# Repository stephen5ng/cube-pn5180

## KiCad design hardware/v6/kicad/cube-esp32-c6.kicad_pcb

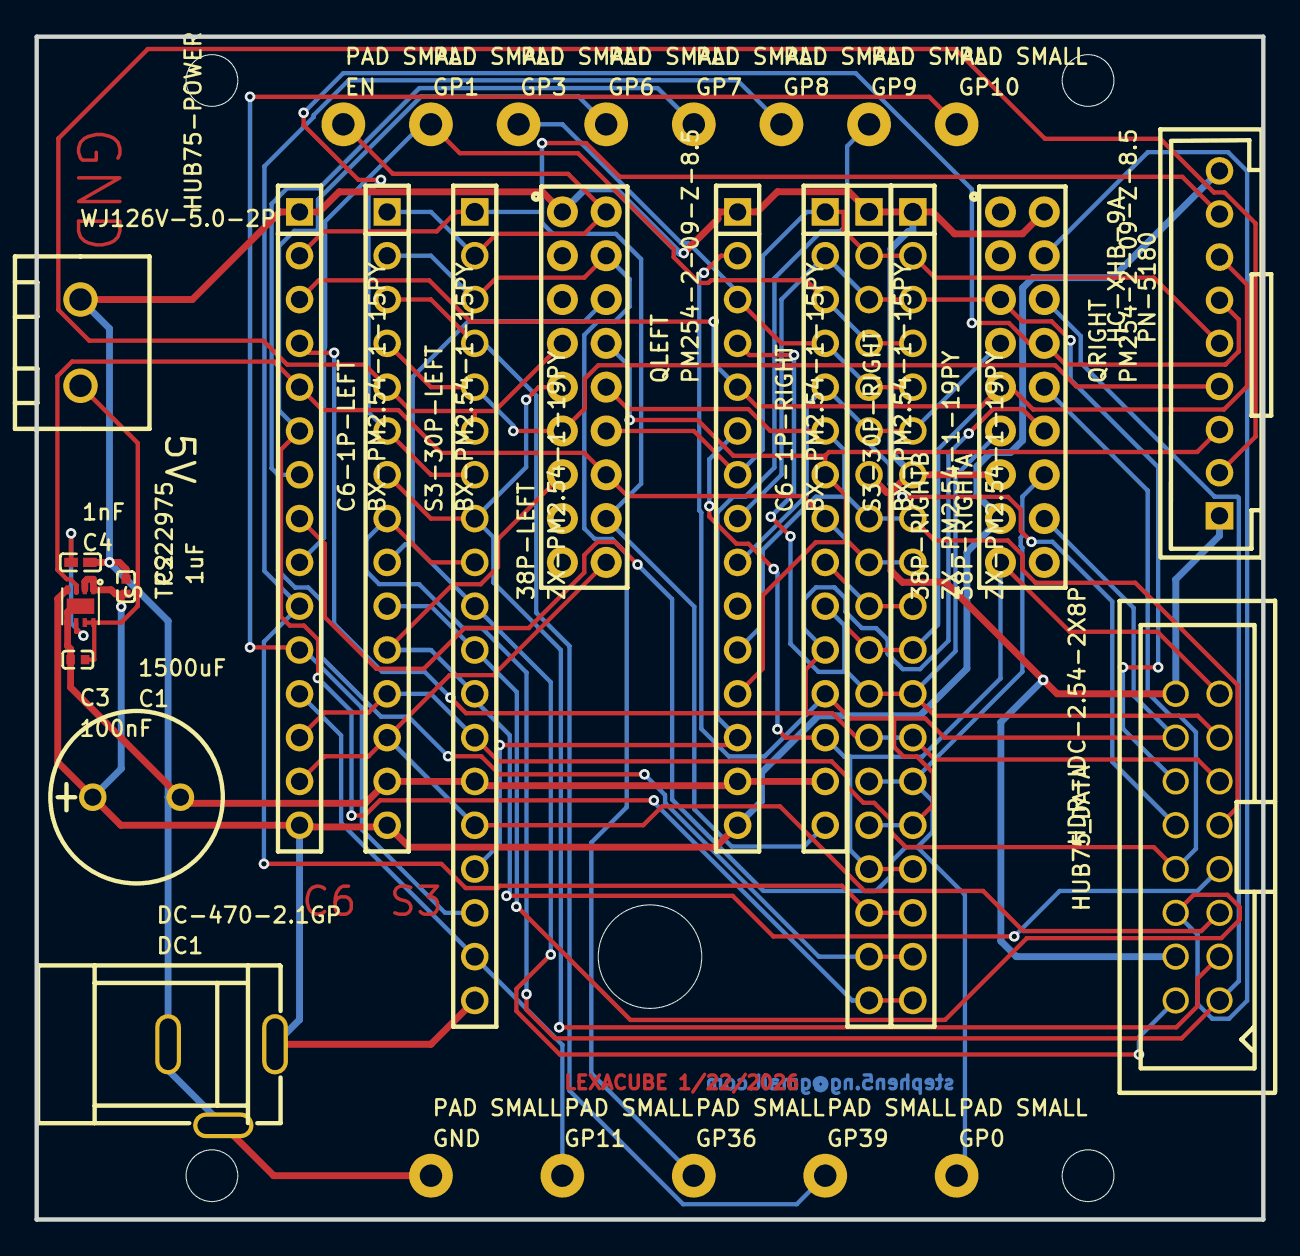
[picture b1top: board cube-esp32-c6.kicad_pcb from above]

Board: 2 copper layers, 71.1 x 68.6 mm, 36 parts (0 on the bottom side), 38 nets.

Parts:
38P-LEFT, 38P-RIGHTA, 38P-RIGHTB: ZX-PM2.54-1-19PY; HDR-TH_19P-P2.54-V-F
C1: 1500uF; CAP-TH_BD10.0-P5.00-D1.0-FD
C2: 1uF; C0402
C3: 100nF; C0402
C4: 1nF; C0402
C6-1P-LEFT, C6-1P-RIGHT: BX-PM2.54-1-15PY; HDR-TH_15P-P2.54-V-F-1
DC1: DC-470-2.1GP; DC-IN-TH_DC-470-2.1GP
EN: PAD SMALL; PADPAD
GND: PAD SMALL; PADPAD
GP0, GP1, GP3, GP6, GP7, GP8, GP9, GP10, GP11, GP36, GP39: PAD SMALL; PADPAD
HUB75-POWER: WJ126V-5.0-2P; CONN-TH_WJ126V-5.0-2P
HUB75_DATA: HDR-IDC-2.54-2X8P; IDC-TH_16P-P2.54_C3406
Hole_gge5988: Hole_gge5988
Hole_gge6018: Hole_gge6018
Hole_gge6033: Hole_gge6033
Hole_gge6048: Hole_gge6048
Hole_gge95769: Hole_gge95769
PN-5180: HC-XHB-9A; CONN-TH_9P_P2.50_HCTL_HC-XHB-9A
QLEFT: PM254-2-09-Z-8.5; HDR-TH_18P-P2.54-V-F-R2-C9-S2.54
QRIGHT: PM254-2-09-Z-8.5; HDR-TH_18P-P2.54-V-F-R2-C9-S2.54
S: TPS22975; WSON-8_L2.0-W2.0-P0.50-TL-EP
S3-30P-LEFT, S3-30P-RIGHT: BX-PM2.54-1-15PY; HDR-TH_15P-P2.54-V-F-1

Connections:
3V: 38P-LEFT.1, C6-1P-LEFT.2, PN-5180.8, QLEFT.16, S3-30P-RIGHT.15
+5V: 38P-LEFT.19, C1.1, C2.2, C6-1P-LEFT.15, C6-1P-RIGHT.15, DC1.1, PN-5180.9, QRIGHT.15, S.1, S.2, S.4, S3-30P-LEFT.15
A: 38P-RIGHTA.8, 38P-RIGHTB.8, C6-1P-RIGHT.11, HUB75_DATA.9, QLEFT.10, S3-30P-RIGHT.6
B: 38P-RIGHTA.6, 38P-RIGHTB.6, C6-1P-RIGHT.9, HUB75_DATA.10, QRIGHT.7, S3-30P-RIGHT.5
B1: 38P-LEFT.8, HUB75_DATA.3, QLEFT.9, S3-30P-LEFT.7
B2: 38P-LEFT.12, HUB75_DATA.7, QLEFT.13, S3-30P-LEFT.11
BUSY: 38P-LEFT.6, PN-5180.2, QLEFT.7, S3-30P-LEFT.5
C: 38P-RIGHTA.13, 38P-RIGHTB.13, C6-1P-LEFT.4, HUB75_DATA.11, QRIGHT.12, S3-30P-RIGHT.11
CLK: 38P-RIGHTA.12, 38P-RIGHTB.12, C6-1P-RIGHT.4, HUB75_DATA.13, QRIGHT.11, S3-30P-RIGHT.10
D: 38P-RIGHTA.3, 38P-RIGHTB.3, C6-1P-RIGHT.8, HUB75_DATA.12, QRIGHT.5, S3-30P-RIGHT.2
E: 38P-LEFT.13, C6-1P-LEFT.13, HUB75_DATA.8, QRIGHT.10, S3-30P-LEFT.12
EN: 38P-LEFT.2, EN.1, QLEFT.2, S3-30P-LEFT.1
G1: 38P-LEFT.10, HUB75_DATA.2, QLEFT.6, S3-30P-LEFT.9
G2: 38P-LEFT.11, HUB75_DATA.6, QRIGHT.4, S3-30P-LEFT.10
GND: 38P-LEFT.14, 38P-RIGHTA.1, 38P-RIGHTA.7, 38P-RIGHTB.1, 38P-RIGHTB.7, C1.2, C2.1, C3.2, C4.2, C6-1P-LEFT.1, C6-1P-RIGHT.1, C6-1P-RIGHT.14, DC1.2, DC1.3, GND.1, HUB75-POWER.1, HUB75_DATA.4, HUB75_DATA.16, PN-5180.1, QLEFT.1, QRIGHT.2, QRIGHT.13, S.5, S.9, S3-30P-LEFT.14, S3-30P-RIGHT.14
GP_0: 38P-RIGHTA.14, 38P-RIGHTB.14, C6-1P-LEFT.8, GP0.1, QRIGHT.14
GP_1: 38P-RIGHTA.4, 38P-RIGHTB.4, C6-1P-LEFT.9, GP1.1, S3-30P-RIGHT.3
GP_3: 38P-RIGHTA.5, 38P-RIGHTB.5, C6-1P-RIGHT.3, GP3.1, S3-30P-RIGHT.4
GP_5: 38P-RIGHTA.10, 38P-RIGHTB.10, C6-1P-LEFT.5, QLEFT.14, S.3, S3-30P-RIGHT.8
GP_6: 38P-RIGHTA.19, 38P-RIGHTB.19, C6-1P-LEFT.6, GP6.1
GP_7: 38P-RIGHTA.18, 38P-RIGHTB.18, C6-1P-LEFT.7, GP7.1
GP_8: 38P-RIGHTA.17, 38P-RIGHTB.17, C6-1P-LEFT.10, GP8.1
GP_9: 38P-LEFT.16, C6-1P-RIGHT.13, GP9.1
GP_10: 38P-LEFT.17, C6-1P-LEFT.11, GP10.1
GP_11: 38P-LEFT.18, C6-1P-LEFT.12, GP11.1
GP_36: 38P-LEFT.3, GP36.1, QLEFT.4, S3-30P-LEFT.2
GP_39: 38P-LEFT.4, GP39.1, S3-30P-LEFT.3
LAT: 38P-RIGHTA.15, 38P-RIGHTB.15, C6-1P-RIGHT.2, HUB75_DATA.14, QRIGHT.16, S3-30P-RIGHT.12
MISO: 38P-LEFT.5, PN-5180.4, QLEFT.11, S3-30P-LEFT.4
MOSI: 38P-RIGHTA.2, 38P-RIGHTB.2, C6-1P-RIGHT.7, PN-5180.5, QLEFT.12, S3-30P-RIGHT.1
NSS: 38P-LEFT.7, PN-5180.6, QRIGHT.8, S3-30P-LEFT.6
OE: 38P-RIGHTA.16, 38P-RIGHTB.16, C6-1P-RIGHT.6, HUB75_DATA.15, QRIGHT.17, S3-30P-RIGHT.13
R1: 38P-LEFT.9, HUB75_DATA.1, QRIGHT.6, S3-30P-LEFT.8
R2: 38P-LEFT.15, C6-1P-LEFT.14, HUB75_DATA.5, QLEFT.18, S3-30P-LEFT.13
RST: 38P-RIGHTA.11, 38P-RIGHTB.11, C6-1P-LEFT.3, C6-1P-RIGHT.5, PN-5180.7, QRIGHT.9, S3-30P-RIGHT.9
SCK: 38P-RIGHTA.9, 38P-RIGHTB.9, C6-1P-RIGHT.12, PN-5180.3, QLEFT.8, S3-30P-RIGHT.7
S_6: C4.1, S.6
S_7: C3.1, HUB75-POWER.2, S.7, S.8

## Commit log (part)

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2026-03-04 Fix .gitignore concatenation issue
2026-03-04 chore: add .claude/ to gitignore
    Local settings and worktrees should not affect version detection.
2026-03-04 chore: remove .claude/settings.local.json from tracking
2026-03-04 Revert "fix: align diag_cubes header columns properly"
    This reverts commit 84daea898105b1be5509784a3671ff68df7a54bd.
2026-03-04 test: force OTA retry
2026-03-04 chore: update cube 6 MAC address to genuine Espressif chip
    Old MAC: 14:33:5C:30:29:EC (counterfeit, WiFi issues)
    New MAC: EC:E3:34:79:8A:BC (genuine Espressif)
    The counterfeit chip had OUI 14:33:5C (not Espressif) and exhibited
    severe WiFi instability (672ms avg ping, 70% packet loss). Replaced
    with genuine Espressif ESP32-D0WD-V3.
2026-03-04 feat: add board type to diagnostics
    Split fw field into:
    - board=v1/v6: board type from cube_board_versions.txt
    - fw=<git-sha>: firmware version for tracking
    Old format: fw=v1
    New format: board=v1|fw=94499de
2026-03-04 feat: show board type in diag_cubes.sh output
    Add BOARD column read from cube_board_versions.txt:
    - v1, v6, v1_with_hall, v6_with_hall
    Falls back to file for old firmware, uses 'board=' field from
    new firmware when available.
2026-03-04 Revert "feat: add board type to diagnostics"
    Board type is now shown in diag_cubes.sh output instead.
    Keeps firmware diagnostic format simpler.
2026-03-05 chore: update cube 4 MAC address to new ESP32 chip
2026-03-05 refactor: rename last_mqtt_message_time to last_activity_time
    UDP diag now resets the auto-sleep timer, so the variable name should
    reflect that it tracks all activity (MQTT + UDP), not just MQTT.
2026-03-05 feat: add board type to diagnostic logs
    JSON log now includes board field (v1/v6/v6_with_hall) for each cube.
2026-03-05 feat: add NFC self-test result to HUB75 boot display
2026-03-05 feat: show only last IP octet on HUB75 boot display
    Also adds test jigs for GPIO 35 and PN5180 hardware testing.
2026-03-08 remove confirmation for all flash
2026-05-10 Add uptime_ms to diag UDP response and host parser
    Appends |uptime_ms=<millis()> to the firmware's diag UDP response string,
    and updates diag_cubes.sh to extract it and include it in the JSONL log.
    https://claude.ai/code/session_01JzmUCJMHirsYcbhHDB5J1h
